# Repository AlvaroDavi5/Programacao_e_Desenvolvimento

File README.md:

# Programacao e Desenvolvimento

### Repositorio Geral de Códigos e Projetos

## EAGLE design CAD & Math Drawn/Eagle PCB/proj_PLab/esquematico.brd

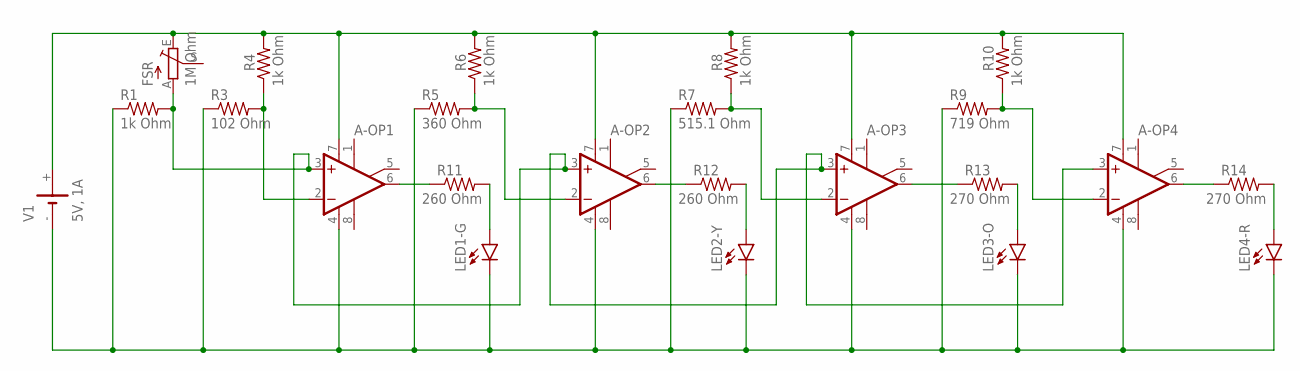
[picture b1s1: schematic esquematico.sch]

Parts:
A-OP1, A-OP2, A-OP3, A-OP4: UA741P; DIL08
FSR: 1M Ohm; CIP20C-4MM
LED1-G, LED2-Y, LED3-O, LED4-R: TLLR4400; LED3MM
R1, R4, R6, R8, R10: 1k Ohm; 0204/5
R3: 102 Ohm; 0204/5
R5: 360 Ohm; 0204/5
R7: 515.1 Ohm; 0204/5
R9: 719 Ohm; 0204/5
R11, R12: 260 Ohm; 0204/5
R13, R14: 270 Ohm; 0204/5
V1: 5V, 1A; CH291-1220LF

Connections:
unnamed: A-OP1.7 (V+), A-OP2.7 (V+), A-OP3.7 (V+), A-OP4.7 (V+), FSR.E, R4.2, R6.2, R8.2, R10.2, V1.+
unnamed: A-OP1.3 (+IN), A-OP2.3 (+IN), A-OP3.3 (+IN), A-OP4.3 (+IN), FSR.A, R1.2
unnamed: A-OP1.4 (V-), A-OP2.4 (V-), A-OP3.4 (V-), A-OP4.4 (V-), LED1-G.K (C), LED2-Y.K (C), LED3-O.K (C), LED4-R.K (C), R1.1, R3.1, R5.1, R7.1, R9.1, V1.-
unnamed: A-OP1.2 (-IN), R3.2, R4.1
unnamed: LED1-G.A, R11.2
unnamed: A-OP2.2 (-IN), R5.2, R6.1
unnamed: A-OP1.6 (OUT), R11.1
unnamed: A-OP2.6 (OUT), R12.1
unnamed: LED2-Y.A, R12.2
unnamed: A-OP3.2 (-IN), R7.2, R8.1
unnamed: A-OP4.2 (-IN), R9.2, R10.1
unnamed: A-OP3.6 (OUT), R13.1
unnamed: LED3-O.A, R13.2
unnamed: A-OP4.6 (OUT), R14.1
unnamed: LED4-R.A, R14.2

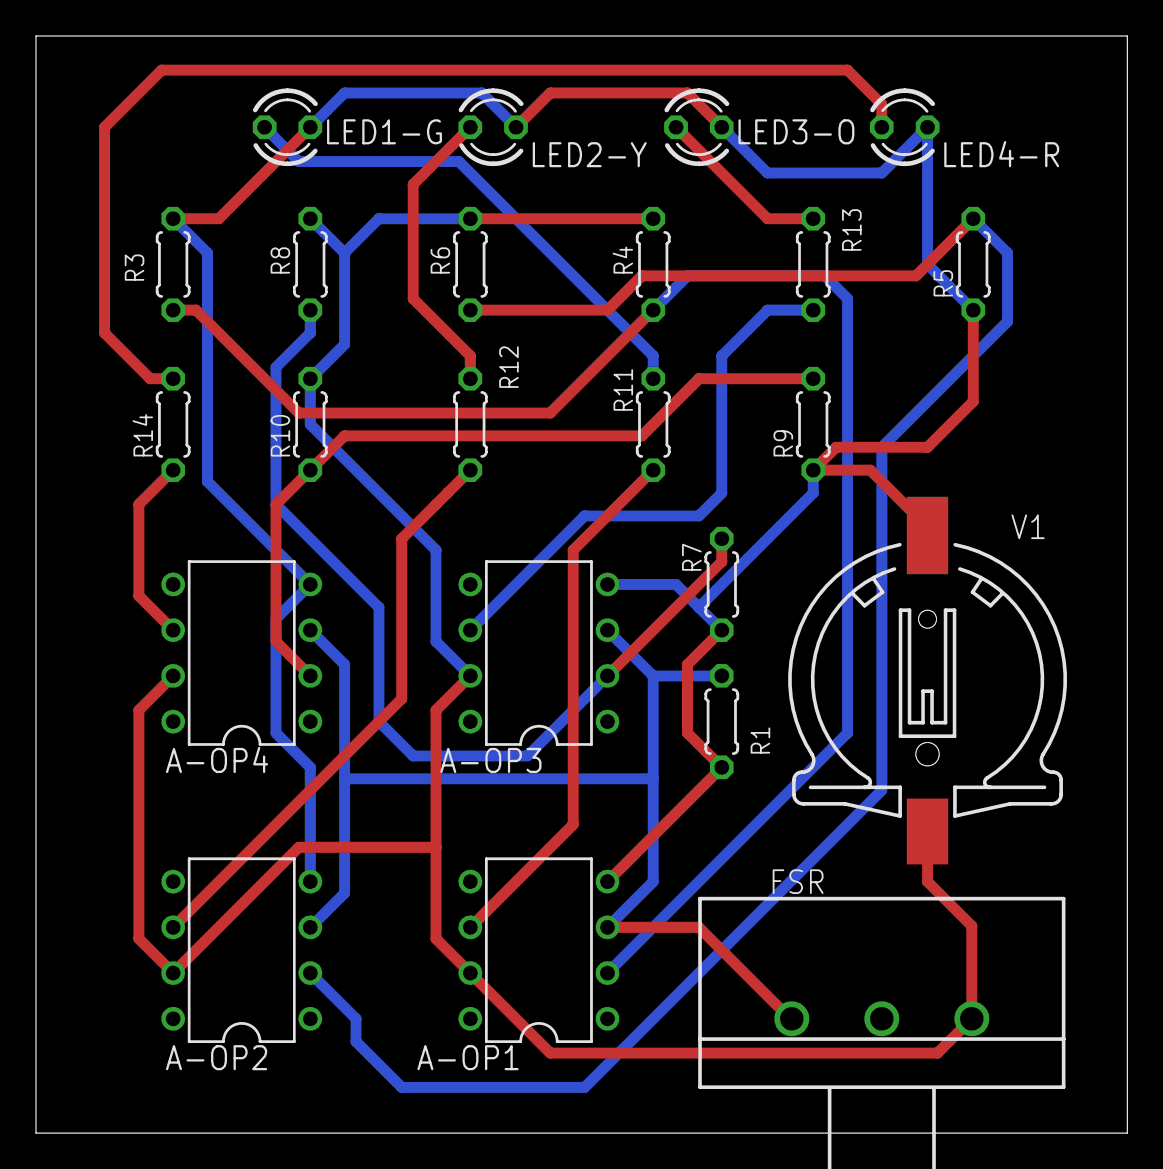
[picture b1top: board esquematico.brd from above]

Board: 2 copper layers, 60.6 x 61.0 mm, 23 parts (0 on the bottom side), 15 nets.

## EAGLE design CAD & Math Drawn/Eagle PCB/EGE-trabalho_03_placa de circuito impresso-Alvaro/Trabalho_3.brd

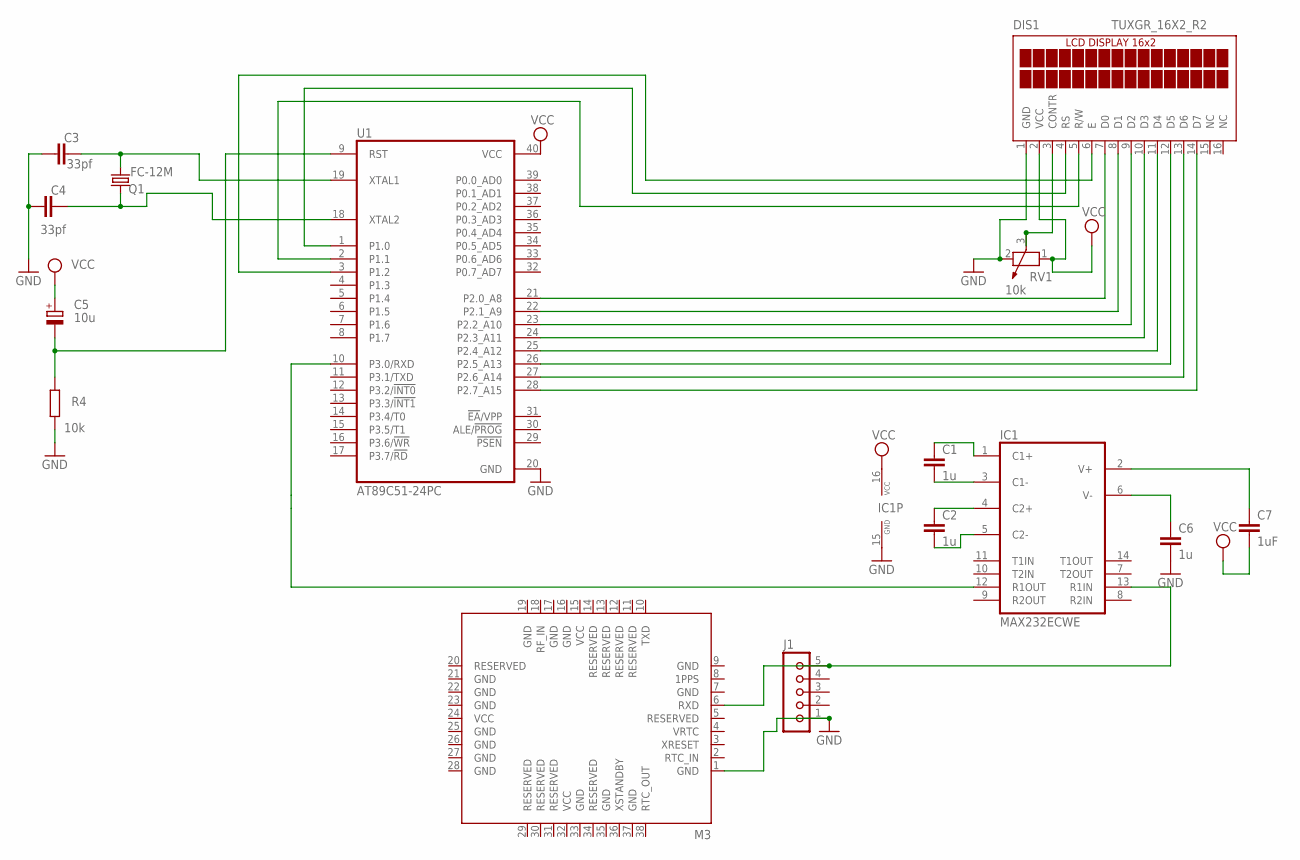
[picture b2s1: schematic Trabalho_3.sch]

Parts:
C1, C2: 1u; C025-025X050
C3, C4: 33pf; C025-025X050
C5: 10u; E2,5-6E
C6: 1u; C0805
C7: 1uF; C0805
DIS1: TUXGR_16X2_R2
IC1: MAX232ECWE; SO16L
J1: JU05
M3: C1011_CONDOR-SMD; 1011
Q1: FC-12M
R4: 10k; 0204/7
RV1: 10k; PT-10
U1: AT89C51-24PC; DIL40

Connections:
GND: C3.1, C4.1, C6.2, DIS1.1 (GND), IC1.15 (GND), J1.1, M3.1 (GND), M3.7 (GND), M3.9 (GND), M3.16 (GND), M3.17 (GND), M3.19 (GND), M3.21 (GND), M3.22 (GND), M3.23 (GND), M3.25 (GND), M3.26 (GND), M3.27 (GND), M3.28 (GND), M3.33 (GND), M3.35 (GND), M3.37 (GND), R4.1, RV1.2, U1.20 (GND)
unnamed: DIS1.3 (CONTR), RV1.3
unnamed: DIS1.4 (RS), U1.1 (P1.0)
unnamed: DIS1.5 (R/W), U1.2 (P1.1)
unnamed: DIS1.6 (E), U1.3 (P1.2)
unnamed: DIS1.7 (D0), U1.21 (P2.0_A8)
unnamed: DIS1.8 (D1), U1.22 (P2.1_A9)
unnamed: DIS1.9 (D2), U1.23 (P2.2_A10)
unnamed: DIS1.10 (D3), U1.24 (P2.3_A11)
unnamed: DIS1.11 (D4), U1.25 (P2.4_A12)
unnamed: DIS1.12 (D5), U1.26 (P2.5_A13)
unnamed: DIS1.13 (D6), U1.27 (P2.6_A14)
unnamed: DIS1.14 (D7), U1.28 (P2.7_A15)
unnamed: C3.2, Q1.2, U1.19 (XTAL1)
unnamed: C5.-, R4.2, U1.9 (RST)
unnamed: C4.2, Q1.1, U1.18 (XTAL2)
unnamed: IC1.12 (R1OUT), U1.10 (P3.0/RXD)
unnamed: C1.1, IC1.1 (C1+)
unnamed: C1.2, IC1.3 (C1-)
unnamed: C2.1, IC1.4 (C2+)
unnamed: C2.2, IC1.5 (C2-)
unnamed: C6.1, IC1.6 (V-)
unnamed: C7.1, IC1.2 (V+)
unnamed: IC1.13 (R1IN), J1.5, M3.6 (RXD)
VCC: C5.+, C7.2, DIS1.2 (VCC), IC1.16 (VCC), M3.15 (VCC), M3.24 (VCC), M3.32 (VCC), RV1.1, U1.40 (VCC)

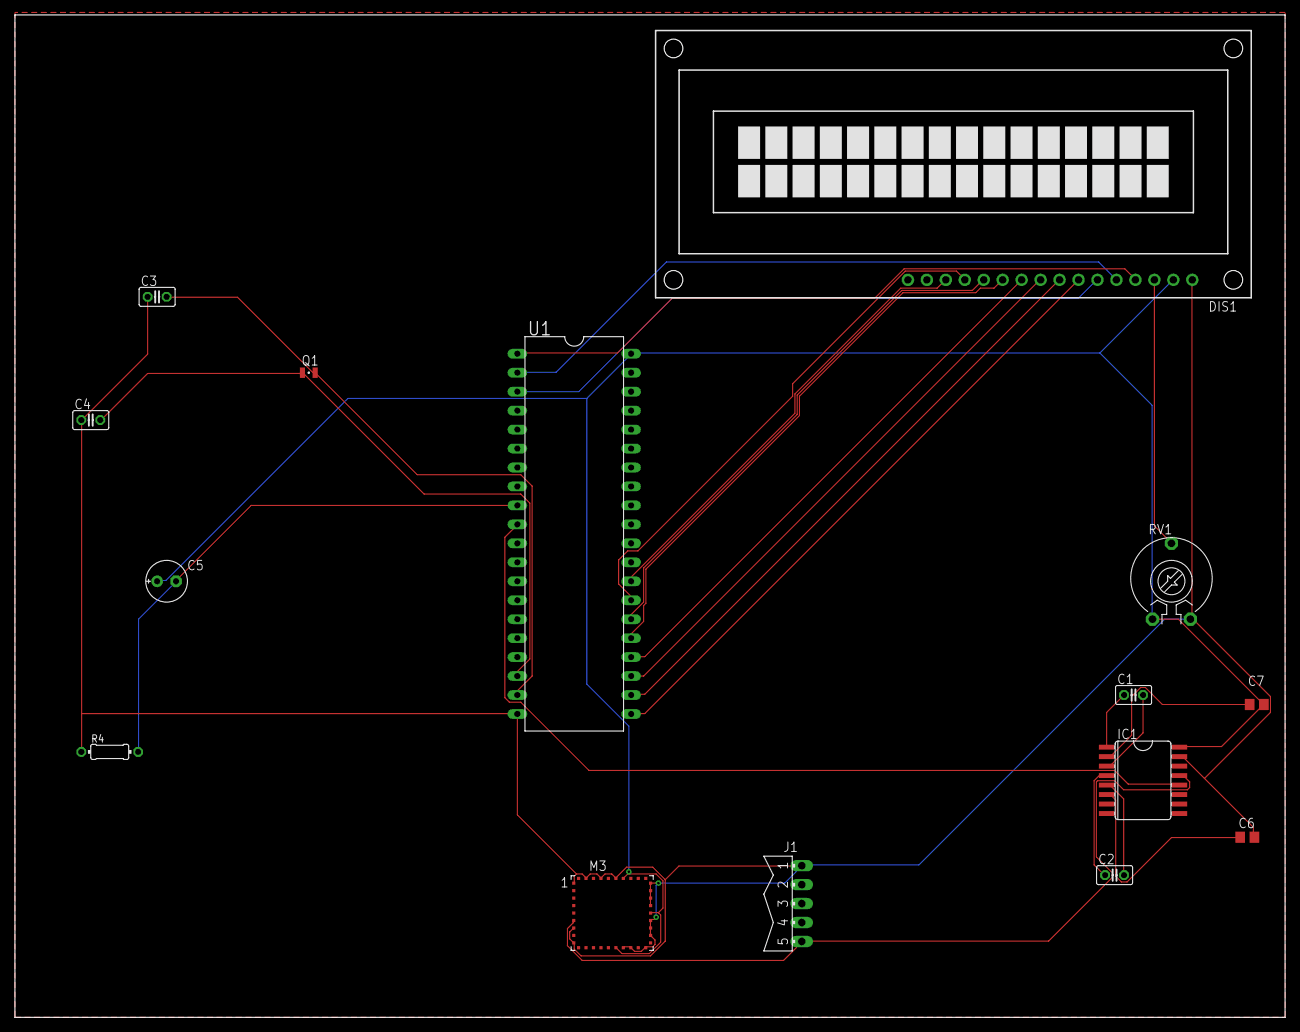
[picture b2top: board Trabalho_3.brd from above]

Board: 2 copper layers, 170.2 x 134.3 mm, 15 parts (0 on the bottom side), 25 nets.

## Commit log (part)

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2020-11-30 EA-6 added
2020-11-30 Versao Final do Trabalho de ProgII
2020-11-30 Versao final do trabalho de prog II
2020-12-02 up game python
2020-12-03 upload
2020-12-18 up test
2020-12-23 criar pdf com python
2020-12-24 reestruturacao
2020-12-24 reestruct
2021-01-10 update game
2021-01-12 rebuild
2021-01-12 generate PDF by HTML with jinja2 and xhtml2pdf
2021-01-20 teste de extensao git no vscode
2021-02-12 webscraping
2021-03-12 rebuild and up
2021-03-16 Novos codigos e mudanças em antigos
2021-03-19 new codes
2021-03-20 programas pegos emprestado kk
2021-03-25 new code
2021-03-31 new programs
2021-03-31 atualizacao de TAD-caixa e de makefile
2021-04-01 status de erros adicionado
2021-04-09 data structure and Jupyter Notebooks
2021-04-11 Principais Estruturas de Dados e SQLite
2021-04-16 new changes
    Ajustes no Pseudo POO
    Ajustes nos Notebooks
    Ajustes e Novos programas Arduino
2021-04-16 sobre ponteiros opacos e flags
2021-04-20 resolucao das atividades no google colab
2021-04-29 reestruturacao de diretorios
2021-05-07 cleaning repeated repos
2021-05-23 workspaces adjusts
2021-05-31 VSCode Settings
    and MySQL Script (SQL with reserved built-in commands)
2021-06-01 removed files moved to another repos
2021-06-01 removed codes moved to another repo
    and updated .gitignore
2021-06-01 removed arduino codes
2021-06-01 removed another codes
2021-06-01 removed markdown
2021-06-01 specify version on requirements
2021-06-02 update workspace
2021-06-03 update workspaces
2021-06-09 added new path to workspace
2021-06-09 pathname on workspace paths
2021-07-04 modified workspace
2021-07-06 ignored dir
2021-07-09 changed workspace paths
2021-07-28 BASIC code sample - MS Word extension
2021-08-05 added unused libs - op
2021-08-05 added unused libs - ch
2021-08-05 use option and install driver on cache
2021-08-05 no option and use driver program file
2021-08-05 no option and use driver program files
2021-08-05 uploaded webdriver program files
2021-08-06 CAD & Math Drawn files
2021-08-06 Circuito RC
2021-08-06 Wheatstone Bridge
2021-08-27 Updated Workspace and repos
2021-08-27 updated datav workspaces
2021-08-29 workspaces configs
2021-09-15 removed NextJs project from workspace
2021-09-18 updated workspace
2021-09-25 updated workspace props
2021-09-29 projeto de Práticas de Laboratório
2021-11-04 updated settings
2021-11-13 updated configs
2021-11-13 updated intellicode configs
2021-11-14 git tests
2021-11-18 VHDL projects samples
2021-11-20 added java launch settings
2021-11-21 updated laucher configs
2021-11-22 removed Huffman Algorithm from workspace
2021-11-25 added parity detector
2021-12-02 added XNOR gate and chave2x2 vhd sources
2021-12-07 added Logic Gates with CMOS on Falstad
2021-12-10 added Programable-Priority Encoder VHDL project
2021-12-21 added priority encoder
2021-12-26 Added new debug configs
2022-01-25 updated settings file
2022-02-01 updated lauch configs
2022-02-06 updated workspace and settings
    - added bracket pair colorization
2022-02-12 added new configs
2022-02-18 added display multiplexer
2022-02-22 added Hello World in various languages
2022-03-03 updated workspace settings
2022-03-19 Added Finite State Machines (FSMs) and new configs
2022-03-23 updated and added workspaces
2022-03-28 added Quiq front-end repo to workspace
2022-06-07 added 3-Bit Shifter VHDL project
2022-06-26 updated workspaces
2022-07-19 updated VS Code settings
2022-08-19 updated settings files
2022-09-25 refact: updated workspaces and settings
2022-09-25 dev: updated workspaces and launcher
2022-10-02 updated IDE settings
2022-10-03 removed socket IO from the workspace
2022-10-23 renamed directory
2022-10-23 added CLog codes
2022-11-04 updated 4 bits adder and subtractor
2022-11-18 refactor: updated setings
2022-11-27 chore: updated VS Code settings to shell environment
2022-12-01 updated VHDL projects
2022-12-20 updated VHDL lab11
2023-02-02 fix: updated project :fire:
2023-05-11 dev: general settings
2023-05-11 dev: workspace settings
2023-06-25 updated settings and workspace
2023-07-08 fix: lab13
2023-07-19 Bump requests from 2.25.1 to 2.31.0 in /NBA web scraping
    Bumps [requests](https://github.com/psf/requests) from 2.25.1 to 2.31.0.
    - [Release notes](https://github.com/psf/requests/releases)
    - [Changelog](https://github.com/psf/requests/blob/main/HISTORY.md)
    - [Commits](https://github.com/psf/requests/compare/v2.25.1...v2.31.0)
    ---
    updated-dependencies:
2023-09-23 updated vscode settings
2023-10-05 updated vscode settings and workspace
2024-01-02 removed VHDL code
    moved to monorepo
2024-06-18 updated workspaces and editor settings
2024-08-03 updated workspaces and launch settings
2024-08-18 upated extensions list (as recomendations)
2024-09-13 updated extensions list
2024-09-13 chore: updated editor settings
2024-11-12 feat: updated extensions list
2024-11-14 chore: editor settings
2025-04-29 refactor: updated vs code and added cursor settings
2025-05-08 updated profiles
2025-05-27 updated extensions
2025-05-29 chore: add container grouping and sorting settings in workspace and settings files
2025-05-29 chore: update VS Code settings with new themes, command center, and container configurations
2025-05-29 chore: update default formatter for Docker Compose in VS Code settings
2025-05-31 chore: enable command center and update workspace settings for improved organization
2025-05-31 Implement feature X to enhance user experience and optimize performance
2025-06-04 refactor: reorganize workspace folder structure for better clarity
2025-06-11 chore: update default formatter to Prettier for consistent code styling
2025-06-11 chore: disable GitHub Copilot next edit suggestions and scminput in workspace settings
2025-06-14 chore: updated VSCode settings and launch options
2025-06-24 refactor: comment out unused service paths in workspace configuration
2025-07-30 refactor: avoiding use libraries for haskell assignment
2025-07-30 chore: moved project
2025-10-24 feat: add project folder for EngSoft2 and comment out Scripts folder in Trabalho workspace
2025-11-21 feat: update workspace settings to enhance explorer and GitHub Copilot functionality
2025-11-21 feat: disable chat agent sessions view location in workspace settings
2025-11-21 feat: remove unused folder reference for AI tools in workspace configuration
2025-12-08 feat: comment out unused folder references in workspace configuration
2025-12-11 feat: update workspace settings to improve terminal and GitHub Copilot functionality
2025-12-12 feat: add new folder reference for Lambdas in workspace configuration
2025-12-16 removed playlist creation script
2026-01-10 feat: update workspace settings to enhance chat and editor configurations
2026-02-02 refactor: remove obsolete folder reference for Projeto_EngSoft2 from workspace configuration
2026-02-04 feat: update folder names in workspace configuration for clarity
2026-03-04 moved to repository
2026-03-04 feat: add folder entries for Go and Rust in workspace configuration
2026-03-04 feat: update default formatter settings and add R language support in workspace configuration
2026-03-09 feat: update editor settings and default formatters in workspace configuration
2026-03-10 feat: update JavaScript and TypeScript settings for improved auto-imports and memory management
2026-03-18 feat: enhance workspace settings with new formatter configurations and commit message generation instructions
2026-03-18 feat: update commit message generation instructions to use conventional format
2026-03-18 feat: update default formatters for chat agent and prompt in workspace settings
2026-04-07 feat: update preferred high contrast light color theme to "Light Modern" in workspace settings
2026-04-18 feat: rename boilerplate projects for clarity in workspace settings
2026-04-22 feat: enable chat MCP gallery and update preferred high contrast light color theme to "Light Modern" in workspace settings
2026-04-22 chore: update project structure and remove unused files
2026-04-23 started logisim folder
2026-04-23 updated logisim project
2026-04-28 chore: update code structure for better maintainability
2026-04-28 fix: update TypeScript SDK path to use workspace folder variable
2026-04-28 chore: update comments from 'Git' to 'Versioning' for clarity
2026-04-28 chore: rename workspace folder from 'Programacao_e_Desenvolvimento' to 'Programacao'
2026-04-29 chore: improve zed settings
2026-04-29 fix: correct indentation for TypeScript SDK path in workspace configuration
2026-04-29 chore: adjust zed settings
2026-05-26 feat: minicomputer changes
2026-05-29 chore: comment out already active language servers and add HTML formatting settings
2026-05-29 chore: add anchors and comments for better organization in settings.json
2026-05-29 feat: add theme overrides for Dracula themes and update formatter settings
2026-05-29 chore: update language server configurations and enable additional servers
2026-05-29 style: add missing newline at end of settings.json
2026-05-29 chore: update language server configurations by disabling unused servers
2026-05-29 updated backup
2026-06-14 feat: added new project for own circuits
2026-06-14 fix: reorder github-copilot-cli configuration and add cursor registry
2026-06-15 fix: update agent_servers configuration to use default_config_options for model
2026-06-16 fix: update workspace settings to enhance chat tool configurations
2026-06-16 fix: update chat tools autoApprove URLs in settings
2026-06-16 fix: configure ESLint settings to never fix issues on save
2026-06-24 Updated minicomputer by logsim
2026-06-24 updated zed patterns
